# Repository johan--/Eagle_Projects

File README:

Eagle files for current Itux.co.za Projects
www.itux.co.za
www.openhardware.co.za
www.house4hack.co.za

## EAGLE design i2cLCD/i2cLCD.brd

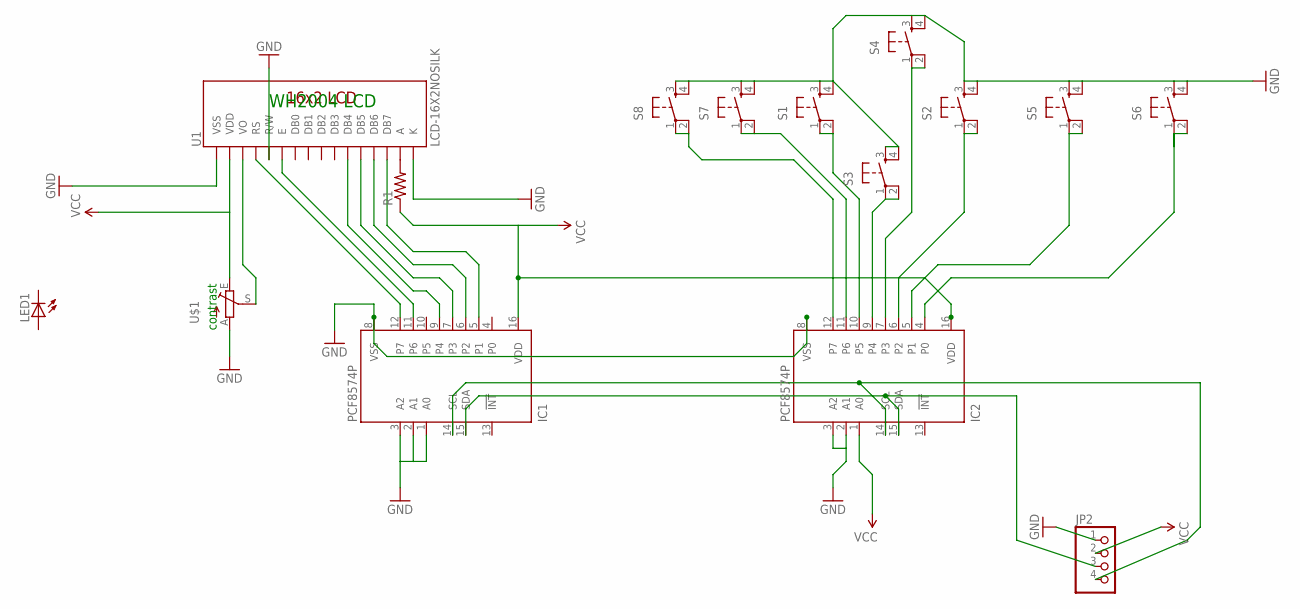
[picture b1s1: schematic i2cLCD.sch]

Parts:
IC1: PCF8574P; DIL16
IC2: PCF8574P; DIL16; MPN PCF8574PN
JP2: PINHD-1X4/90; 1X04/90
LED1: LED1206; LED-1206
R1: RESISTORPTH-1/4W; AXIAL-0.4
S1, S2, S3, S4, S5, S6, S7, S8: TAC_SWITCHPTH; TACTILE-PTH
U1: LCD-16X2NOSILK; LCD-16X2_NOSILK
U$1: TRIM_EU-CA9V; CA9V

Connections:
unnamed: U1.3 (VO), U$1.S
unnamed: R1.P$2 (2), U1.15 (A)
unnamed: IC1.14 (SCL), IC2.14 (SCL), JP2.4
unnamed: IC1.5 (P1), U1.14 (DB7)
unnamed: IC1.6 (P2), U1.13 (DB6)
unnamed: IC1.7 (P3), U1.12 (DB5)
unnamed: IC1.9 (P4), U1.11 (DB4)
unnamed: IC1.11 (P6), U1.6 (E)
unnamed: IC1.12 (P7), U1.4 (RS)
unnamed: IC1.15 (SDA), IC2.15 (SDA), JP2.3
unnamed: IC2.10 (P5), S1.1, S1.2
unnamed: IC2.9 (P4), S3.1, S3.2
unnamed: IC2.7 (P3), S4.1, S4.2
unnamed: IC2.6 (P2), S2.1, S2.2
unnamed: IC2.5 (P1), S5.1, S5.2
unnamed: IC2.4 (P0), S6.1, S6.2
unnamed: IC2.11 (P6), S7.1, S7.2
unnamed: IC2.12 (P7), S8.1, S8.2
unnamed: IC1.1 (A0), IC1.2 (A1), IC1.3 (A2), IC1.8 (VSS), IC2.2 (A1), IC2.3 (A2), IC2.8 (VSS), JP2.1, S1.3, S1.4, S2.3, S2.4, S3.3, S3.4, S4.3, S4.4, S5.3, S5.4, S6.3, S6.4, S7.3, S7.4, S8.3, S8.4, U1.1 (VSS), U1.5 (R/W), U1.16 (K), U$1.A
VCC: IC1.16 (VDD), IC2.1 (A0), IC2.16 (VDD), JP2.2, R1.P$1 (1), U1.2 (VDD), U$1.E

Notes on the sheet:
contrast
WH2004 LCD

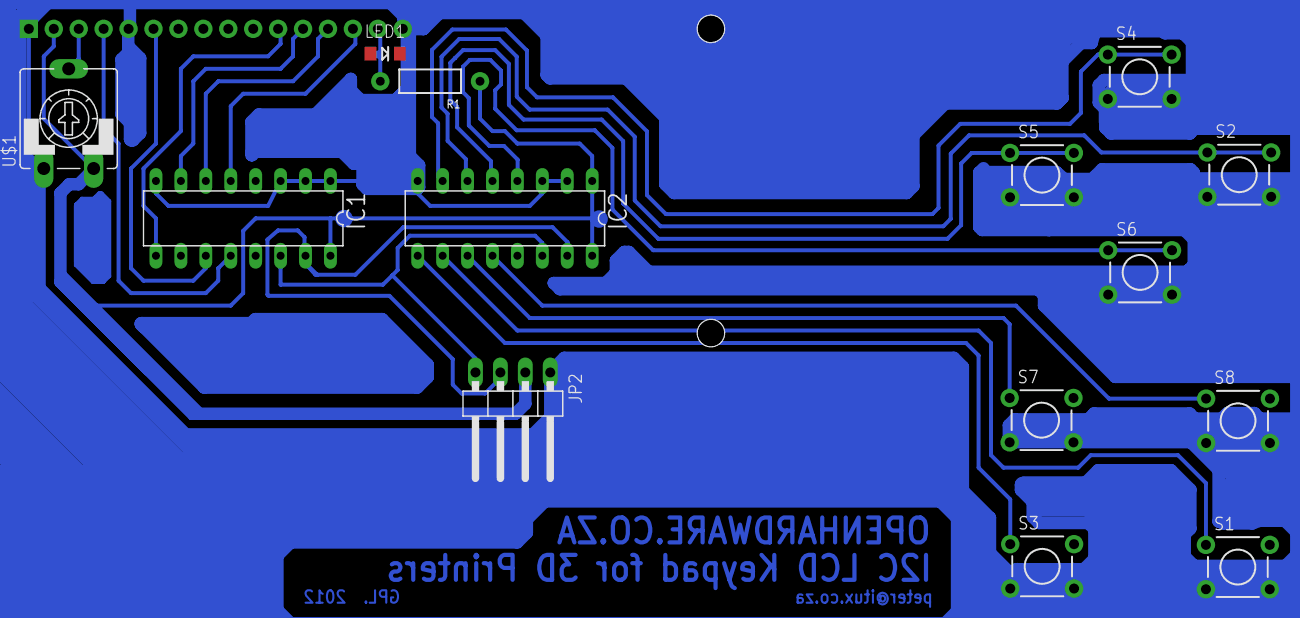
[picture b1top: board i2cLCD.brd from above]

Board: 2 copper layers, 15 parts (0 on the bottom side), 20 nets.

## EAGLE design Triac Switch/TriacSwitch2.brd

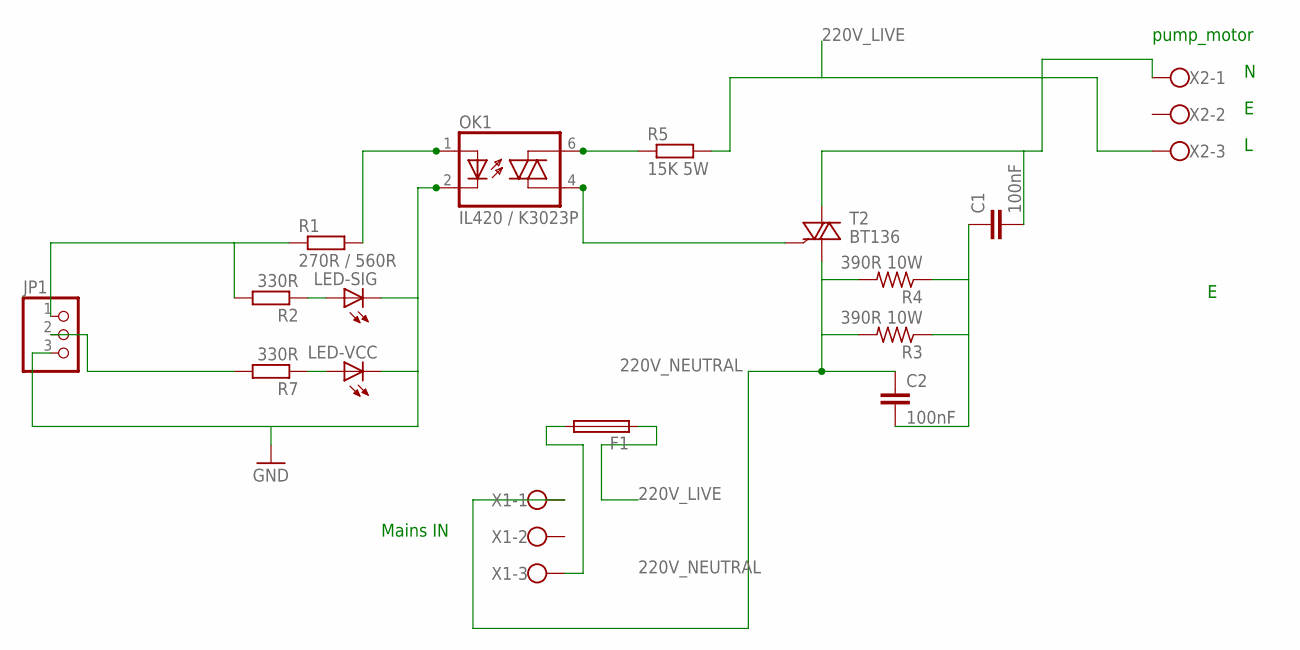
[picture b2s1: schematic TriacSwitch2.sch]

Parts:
C1, C2: 100nF; C150-054X183
F1: GSH15; MPN 64900001039
JP1: PINHD-1X3; 1X03
LED-SIG: LED3MM
LED-VCC: LED3MM
OK1: IL420 / K3023P; DIL06
R1: 270R / 560R; 0204/7
R2, R7: 330R; 0204/7
R3, R4: 390R 10W; 0922/22
R5: 15K 5W; 0617/22
T2: BT136; TO220AB
X1, X2: W237-103

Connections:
220V_LIVE: F1.1, R5.2, X2.3
220V_NEUTRAL: C2.1, R3.2, R4.2, T2.1 (A1), X1.1
GND: JP1.3, LED-SIG.K (C), LED-VCC.K (C), OK1.2 (C)
unnamed: OK1.4 (A1), T2.3 (G)
unnamed: F1.2, X1.3
unnamed: JP1.1, R1.1, R2.2
unnamed: LED-SIG.A, R2.1
unnamed: OK1.6 (A2), R5.1
unnamed: C1.1, C2.2, R3.1, R4.1
unnamed: OK1.1 (A), R1.2
unnamed: LED-VCC.A, R7.1
unnamed: JP1.2, R7.2
unnamed: C1.2, T2.2 (A2), X2.1

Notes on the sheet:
Mains IN
pump_motor

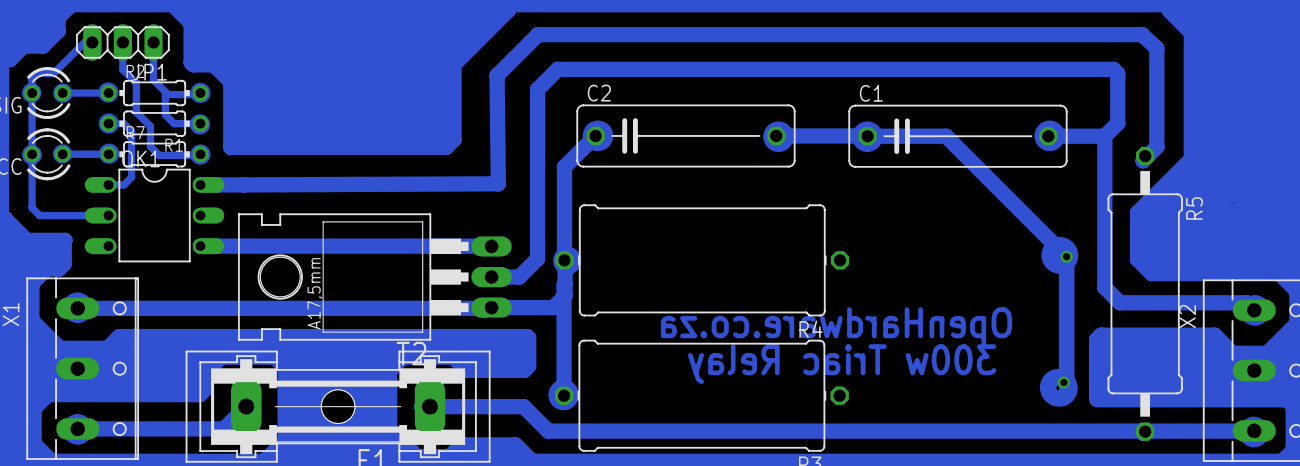
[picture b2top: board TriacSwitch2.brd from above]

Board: 2 copper layers, 16 parts (0 on the bottom side), 13 nets.

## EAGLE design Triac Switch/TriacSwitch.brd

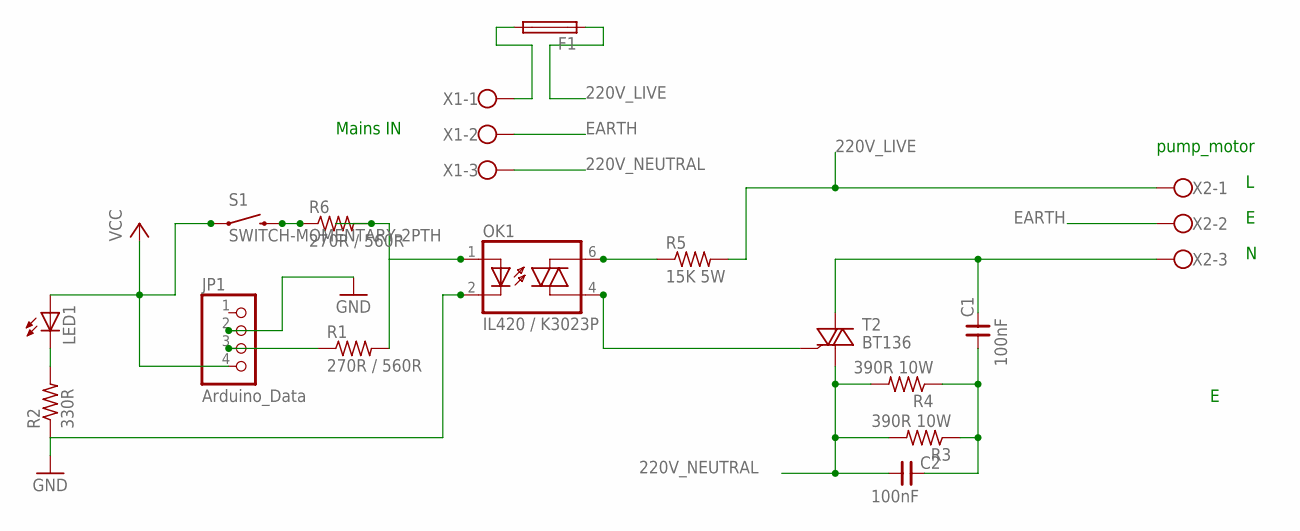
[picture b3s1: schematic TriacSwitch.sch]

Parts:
C1, C2: 100nF; C050-110X055
F1: KS10H
JP1: Arduino_Data; 1X04
LED1: LED3MM
OK1: IL420 / K3023P; DIL06
R1, R6: 270R / 560R; 0207/10
R2: 330R; 0207/10
R3, R4: 390R 10W; 0922/22
R5: 15K 5W; 0617/17
S1: SWITCH-MOMENTARY-2PTH; TACTILE-PTH
T2: BT136; TO220AB
X1, X2: W237-103

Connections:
220V_LIVE: F1.1, R5.2, X2.1
220V_NEUTRAL: C2.1, R3.2, R4.2, T2.1 (A1), X1.3
EARTH: X1.2, X2.2
GND: JP1.2, OK1.2 (C), R2.1
unnamed: OK1.4 (A1), T2.3 (G)
unnamed: F1.2, X1.1
unnamed: JP1.3, R1.1
unnamed: LED1.K (C), R2.2
unnamed: R6.1, S1.3 (2)
unnamed: OK1.6 (A2), R5.1
unnamed: C1.1, C2.2, R3.1, R4.1
unnamed: OK1.1 (A), R1.2, R6.2
unnamed: C1.2, T2.2 (A2), X2.3
VCC: JP1.4, LED1.A, S1.1

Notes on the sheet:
Mains IN
pump_motor

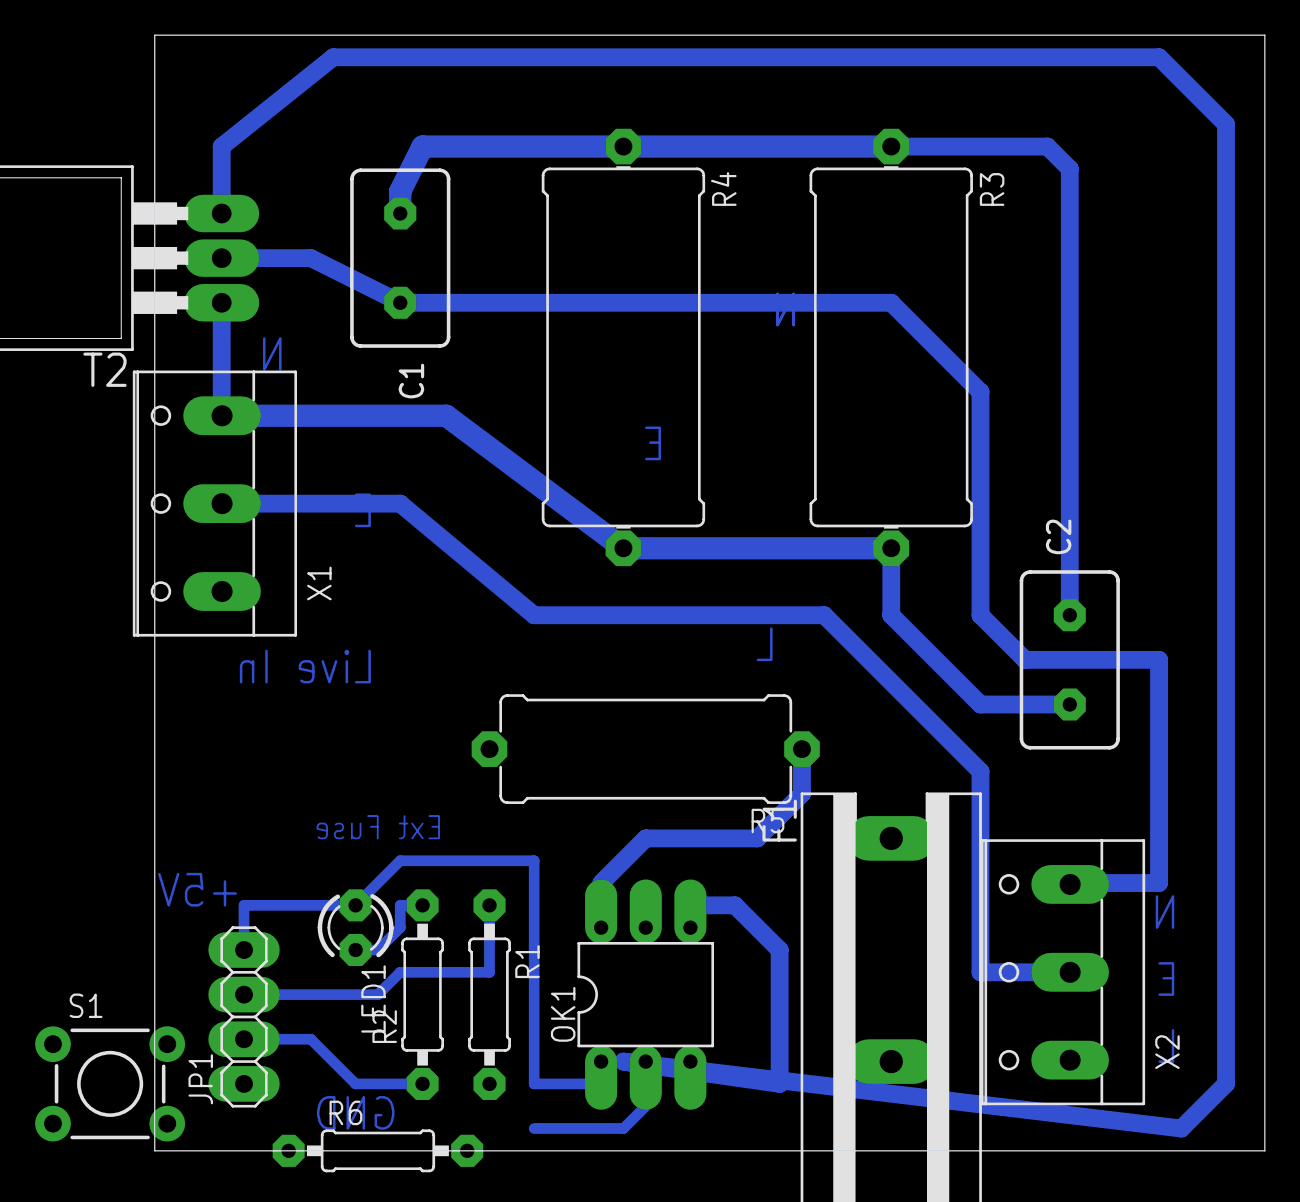
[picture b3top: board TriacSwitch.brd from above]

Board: 2 copper layers, 63.2 x 63.5 mm, 16 parts (0 on the bottom side), 14 nets.

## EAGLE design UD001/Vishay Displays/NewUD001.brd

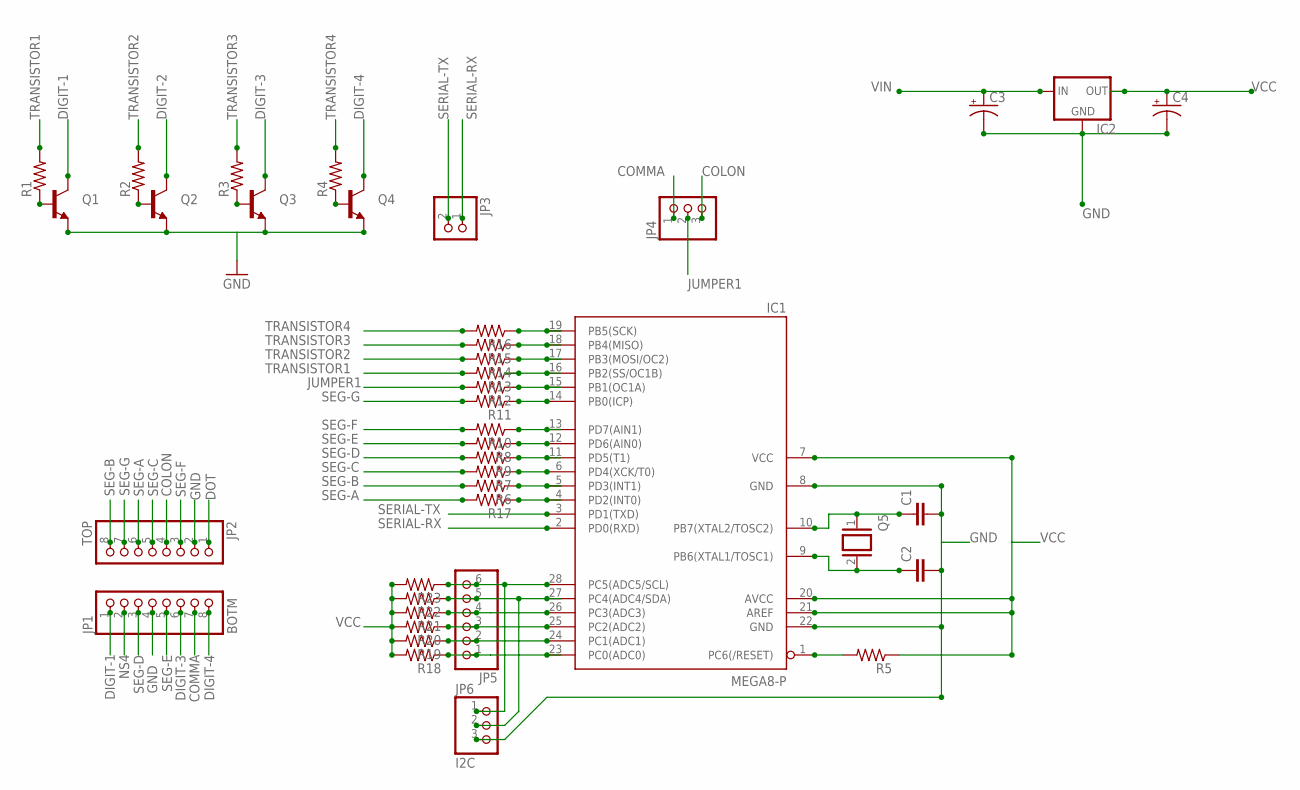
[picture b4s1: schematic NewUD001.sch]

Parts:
C1, C2: CAPKIT; CAP-PTH-SMALL-KIT
C3: CAP_POLPTH1; CPOL-RADIAL-100UF-25V
C4: CAP_POLPTH2; CPOL-RADIAL-10UF-25V
IC1: MEGA8-P; DIL28-3
IC2: V_REG_78XX-TO-220; TO-220-ALT
JP1: BOTM; 1X08
JP2: TOP; 1X08
JP3: PINHD-1X2; 1X02
JP4: PINHD-1X3; 1X03
JP5: PINHD-1X6; 1X06
JP6: I2C; 1X03
Q1, Q2, Q3, Q4: TRANSISTOR_NPNSOT23; SOT23
Q5: XTAL/S; QS
R1, R2, R3, R4, R5, R6, R7, R8, R9, R10, R11, R12, R13, R14, R15, R16, R17, R18, R19, R20, R21, R22, R23: RESISTORKIT; AXIAL-0.3-KIT

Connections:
COLON: JP2.4, JP4.3
COMMA: JP1.7, JP4.1
DIGIT-1: JP1.1, Q1.3 (C)
DIGIT-2: Q2.3 (C)
DIGIT-3: JP1.6, Q3.3 (C)
DIGIT-4: JP1.8, Q4.3 (C)
DOT: JP2.1
GND: C2.2, C3.2 (-), C4.2 (-), IC1.8 (GND), IC1.22 (GND), IC2.GND, JP1.4, JP2.2, JP6.3, Q1.2 (E), Q2.2 (E), Q3.2 (E), Q4.2 (E)
JUMPER1: JP4.2, R12.P$2 (2)
unnamed: C1.1, IC1.10 (PB7(XTAL2/TOSC2)), Q5.1
unnamed: Q1.1 (B), R1.P$1 (1)
unnamed: Q2.1 (B), R2.P$1 (1)
unnamed: Q3.1 (B), R3.P$1 (1)
unnamed: Q4.1 (B), R4.P$1 (1)
unnamed: C2.1, IC1.9 (PB6(XTAL1/TOSC1)), Q5.2
unnamed: IC1.1 (PC6(/RESET)), R5.P$2 (2)
unnamed: IC1.5 (PD3(INT1)), R6.P$1 (1)
unnamed: IC1.6 (PD4(XCK/T0)), R7.P$1 (1)
unnamed: IC1.11 (PD5(T1)), R9.P$1 (1)
unnamed: IC1.28 (PC5(ADC5/SCL)), JP5.6, JP6.1, R23.P$1 (1)
unnamed: IC1.27 (PC4(ADC4/SDA)), JP5.5, JP6.2, R22.P$1 (1)
unnamed: IC1.12 (PD6(AIN0)), R8.P$1 (1)
unnamed: IC1.26 (PC3(ADC3)), JP5.4, R21.P$1 (1)
unnamed: IC1.13 (PD7(AIN1)), R10.P$1 (1)
unnamed: IC1.14 (PB0(ICP)), R11.P$1 (1)
unnamed: IC1.15 (PB1(OC1A)), R12.P$1 (1)
unnamed: IC1.16 (PB2(SS/OC1B)), R13.P$1 (1)
unnamed: IC1.17 (PB3(MOSI/OC2)), R14.P$1 (1)
unnamed: IC1.18 (PB4(MISO)), R15.P$1 (1)
unnamed: IC1.19 (PB5(SCK)), R16.P$1 (1)
unnamed: IC1.4 (PD2(INT0)), R17.P$1 (1)
unnamed: IC1.25 (PC2(ADC2)), JP5.3, R20.P$1 (1)
unnamed: IC1.24 (PC1(ADC1)), JP5.2, R19.P$1 (1)
unnamed: IC1.23 (PC0(ADC0)), JP5.1, R18.P$1 (1)
NS4: JP1.2
SEG-A: JP2.6, R17.P$2 (2)
SEG-B: JP2.8, R6.P$2 (2)
SEG-C: JP2.5, R7.P$2 (2)
SEG-D: JP1.3, R9.P$2 (2)
SEG-E: JP1.5, R8.P$2 (2)
SEG-F: JP2.3, R10.P$2 (2)
SEG-G: JP2.7, R11.P$2 (2)
SERIAL-RX: IC1.2 (PD0(RXD)), JP3.1
SERIAL-TX: IC1.3 (PD1(TXD)), JP3.2
TRANSISTOR1: R1.P$2 (2), R13.P$2 (2)
TRANSISTOR2: R2.P$2 (2), R14.P$2 (2)
TRANSISTOR3: R3.P$2 (2), R15.P$2 (2)
TRANSISTOR4: R4.P$2 (2), R16.P$2 (2)
VCC: C4.1 (+), IC1.7 (VCC), IC1.20 (AVCC), IC1.21 (AREF), IC2.OUT, R5.P$1 (1), R18.P$2 (2), R19.P$2 (2), R20.P$2 (2), R21.P$2 (2), R22.P$2 (2), R23.P$2 (2)
VIN: C3.1 (+), IC2.IN

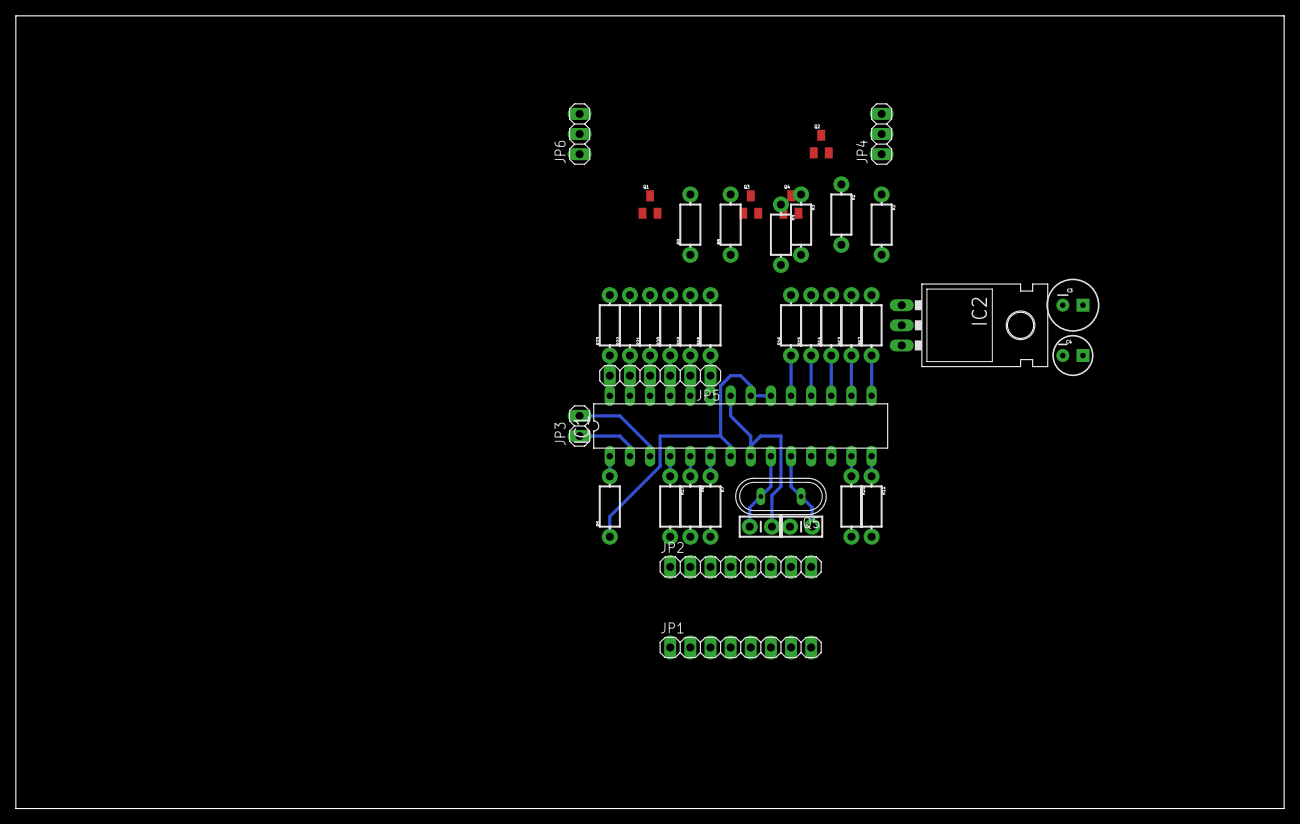
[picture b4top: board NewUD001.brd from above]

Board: 2 copper layers, 160.0 x 100.0 mm, 40 parts (0 on the bottom side), 47 nets.

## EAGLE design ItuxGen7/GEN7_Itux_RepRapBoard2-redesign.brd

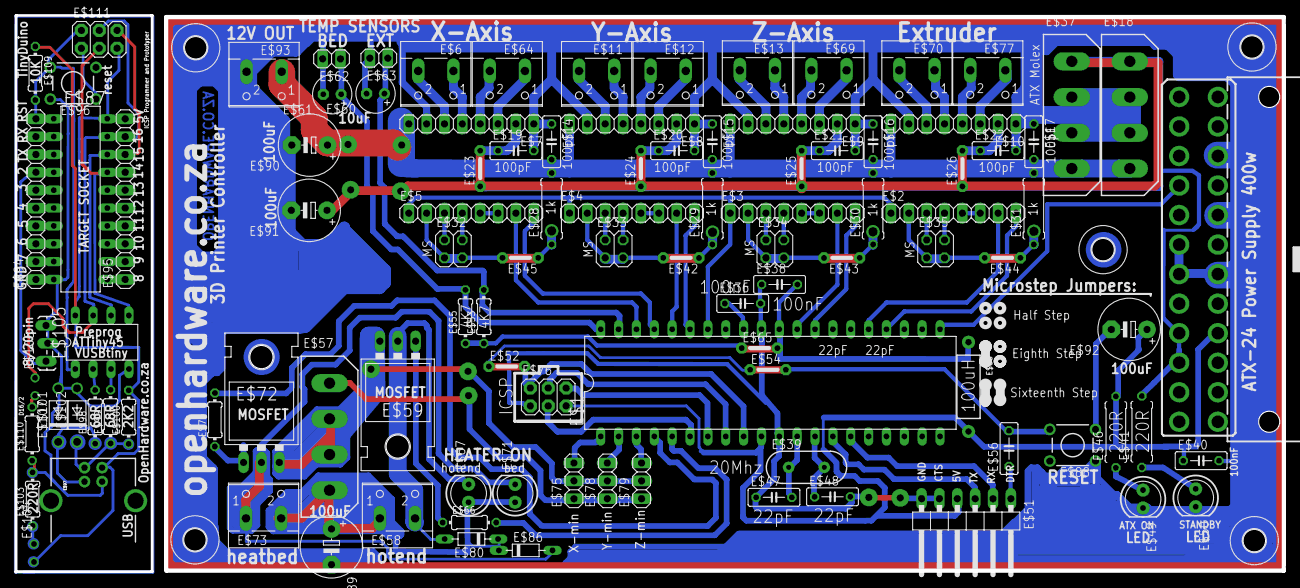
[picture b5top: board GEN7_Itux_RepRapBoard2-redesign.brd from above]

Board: 2 copper layers, 180.4 x 79.2 mm, 110 parts (0 on the bottom side), 38 nets.

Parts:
E$1: DIL40
E$2, E$3, E$4, E$5, E$7, E$8, E$9, E$10: 1X08
E$6, E$11, E$12, E$13, E$58, E$64, E$69, E$70, E$73, E$77, E$93: W237-102
E$14, E$15, E$16, E$17, E$19, E$20, E$21, E$22, E$36, E$38, E$40, E$47, E$48, E$56: C050-025X075
E$18, E$37, E$57: 9090-4V
E$23, E$24, E$25, E$26, E$42, E$43, E$44, E$45, E$52, E$54, E$65: 05
E$27: ATX24_RIGHT_ANGLE
E$28, E$29, E$30, E$31, E$41, E$46: 0309/10
E$32, E$33, E$34, E$35: 2X02
E$39: HC49US
E$49, E$50, E$67, E$71: LED5MM
E$51: 1X06/90
E$53, E$55, E$66, E$74, E$109, E$110: 0204/7
E$59, E$72: TO-220-ALT
E$60, E$61: E2,5-6
E$62, E$63: 1X02
E$68: AXIAL-0.5
E$75, E$78, E$79: 1X03
E$76, E$111: 2X03
E$80, E$86: D-7.5
E$81, E$82, E$83, E$84, E$85: 3,2
E$87: DIL20
E$88, E$96: TL1105
E$89, E$90, E$91, E$92: E5-8,5
E$94, E$95: 1X10
E$97: USB-B-PTH
E$98: 68RD+; 0204/7
E$99: 68Rd-; 0204/7
E$100, E$103: 2K2; 0204/7
E$101, E$102: DO41-7
E$104, E$107: LED3MM-NS
E$105: DIL8
E$106: 1X03_LOCK_LONGPADS

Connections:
5VRAIL: E$26.1, E$37.1
12VRAIL: E$8.8, E$9.8, E$10.8, E$14.2, E$15.2, E$16.2, E$17.2
GNDPLANE: E$7.1, E$8.1, E$8.7, E$9.1, E$9.7, E$10.7, E$14.1, E$15.1, E$16.1, E$18.3, E$19.2, E$20.2, E$21.2, E$37.2, E$37.3
S$18: E$7.2, E$19.1, E$23.2
S$19: E$10.1, E$17.1, E$22.2
S$20: E$8.2, E$20.1, E$24.2
S$23: E$9.2, E$21.1, E$25.2
S$25: E$10.2, E$22.1, E$26.2
S$26: E$5.2, E$32.1
S$27: E$5.3, E$32.2
S$28: E$5.4, E$32.4
S$29: E$4.2, E$33.1
S$30: E$4.3, E$33.2
S$31: E$4.4, E$33.4
S$32: E$3.2, E$34.1
S$33: E$3.3, E$34.2
S$34: E$3.4, E$34.4
S$35: E$2.2, E$35.1
S$36: E$2.3, E$35.2
S$37: E$2.4, E$35.4
S$38: E$5.5, E$5.6
S$39: E$4.5, E$4.6
S$40: E$3.5, E$3.6
S$41: E$2.5, E$2.6
S$46: E$32.3, E$45.2
S$47: E$1.36, E$4.7
S$48: E$1.38, E$5.7
S$49: E$1.34, E$2.1, E$3.1, E$4.1, E$5.1
S$50: E$33.3, E$42.2
S$51: E$34.3, E$43.2
S$52: E$35.3, E$44.2
S$56: E$1.25, E$2.7
S$57: E$1.37, E$5.8
S$58: E$1.29, E$3.7
S$59: E$1.35, E$4.8
S$60: E$1.28, E$3.8
S$61: E$1.24, E$2.8
S$121: E$1.6, E$76.3

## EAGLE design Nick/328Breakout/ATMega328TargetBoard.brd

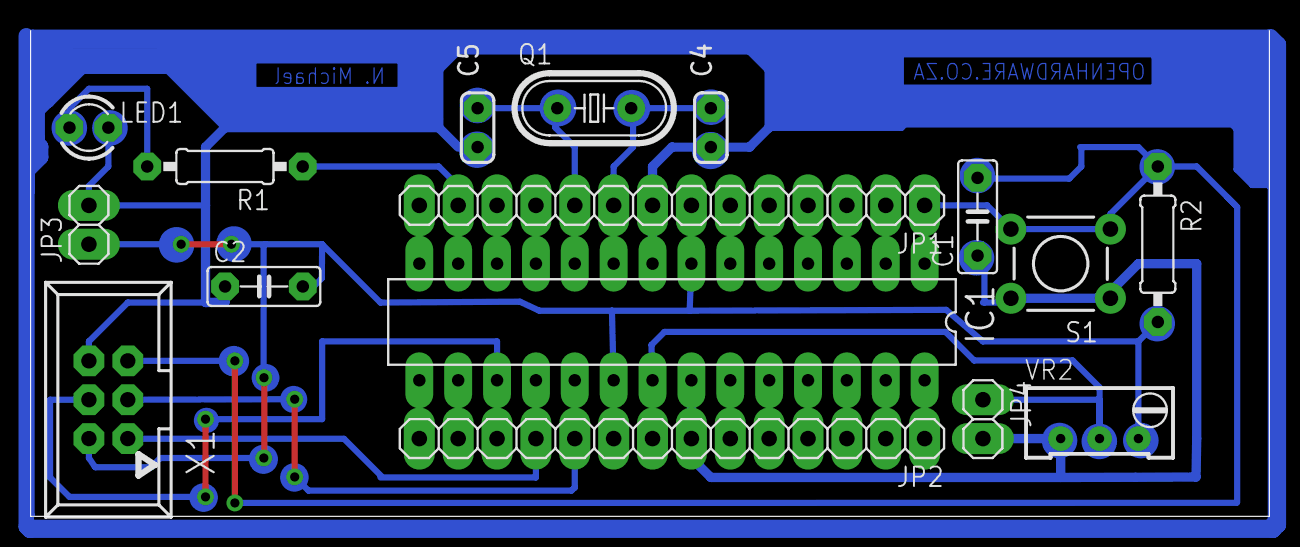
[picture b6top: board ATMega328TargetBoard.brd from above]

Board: 2 copper layers, 81.0 x 31.7 mm, 16 parts (0 on the bottom side), 29 nets.

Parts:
C1, C2: 0.1uF; C050-025X075
C4, C5: 22pF; C025-040X018
IC1: ATMEGA168-PU; DIL28-3
JP1: 1-14; 1X14
JP2: 15-28; 1X14
JP3: Power; 1X02
JP4: 3V3; 1X02
LED1: red; LED3MM
Q1: 16MHz; HC49U-V
R1: 1K; 0207/10
R2: 10K; 0207/10
S1: Reset Switch; TACTILE-PTH
VR2: 5K; RTRIM64W
X1: 057-006-1

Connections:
2_RX: IC1.2, JP1.2
3_TX: IC1.3, JP1.3
4: IC1.4, JP1.4
5: IC1.5, JP1.5
6: IC1.6, JP1.6
9: C4.2, IC1.9, Q1.2
10: C5.2, IC1.10, Q1.1
11: IC1.11, JP1.11
12: IC1.12, JP1.12
13: IC1.13, JP1.13, R1.1
14: IC1.14, JP1.14
15: IC1.15, JP2.14
16: IC1.16, JP2.13
17_MOSI: IC1.17, JP2.12, X1.4
18_MISO: IC1.18, JP2.11
21: JP4.1, VR2.2
23: IC1.23, JP2.6
24: IC1.24, JP2.5
25: IC1.25, JP2.4
26: IC1.26, JP2.3
27: IC1.27, JP2.2
28: IC1.28, JP2.1
+5V: C2.2, IC1.7, IC1.20, JP1.7, JP2.9, JP3.1, R2.2, VR2.3
GND: C2.1, C4.1, C5.1, IC1.8, JP1.8, JP3.2, LED1.K, X1.6
unnamed: LED1.A, R1.2
S$2: IC1.21, JP2.8
S$3: IC1.1, JP1.1, R2.1, S1.3, S1.4
S$5: IC1.22, JP2.7, JP4.2, S1.1, S1.2, VR2.1
S$8: IC1.19, JP2.10

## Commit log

2012-07-28 new file: Aquaponics/V2.0/Aquaponics Controller version 2.brd
2012-08-02 Etched Copies
2012-08-05 Added AVR-Burner with Script and Firmware files
2012-08-05 Added AVR-Burher start script for Terminal-less running
2012-08-07 Broke Gen7 PCB
2012-08-11 Successful test of AVR-CDC-2313 with 16Mhz and DTR
2012-08-19 New ItuxGEN7 + TinyDuino Gerbers
2012-09-07 Added AVR-Burner PCB
2012-09-08 Added revised Optocoupler choice to Triac Switch
2012-09-30 Added Pinout to UD001 (Vishay) after successful test
2012-10-02 Fixed GND connections on AVR-Burner (Thanks Freddie)
2012-10-02 Added LCDuino Backpack for HD44780s
2012-10-09 Triac2
2012-10-19 Added i2c LCD
2013-07-01 Clean up

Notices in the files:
i2cLCD/i2cLCD.brd:
GPL.  2012
parts and their libraries:
SparkFun-Passives: Licensing: CC v3.0 Share-Alike You are welcome to use this library for commercial purposes.
